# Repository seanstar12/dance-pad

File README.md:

# dance-pad
Code and schematics for Dance Dance Revolution - DDR - FSR sensor upgrade.

# Plan
Use one MEGA238P per arrow to read & convert the 4 FSR values into a pressed/not-pressed signal. 
Use 25 SK6812 LEDs to light up the panel when pressed and show animations when idle.

# Parts
- Arduino-pro-mini clone
- MCP2125 - CAN - interface with Teensy
- Teensy 3.2 - interface with DDR cabinet
- SK6812 - 'Neopixel' LEDs
- FSR - x32 - 4 per tile
- ['Dance Sensor'](https://www.aliexpress.com/item/4000438156295.html) from aliexpress for the TPU shell.
- [FSR](https://www.aliexpress.com/item/4000765691363.html) from aliexpress.

# Why
I have a DDR cabinet, and I am tired of dealing with stuck sensors. This will let me 
calibrate the dance pad on the fly and never have to deal with it again. I've 
wanted to create a CANBus network for a while, and this gives me an excuse to use 
the box of pro-mini clones that I've had for a while now.

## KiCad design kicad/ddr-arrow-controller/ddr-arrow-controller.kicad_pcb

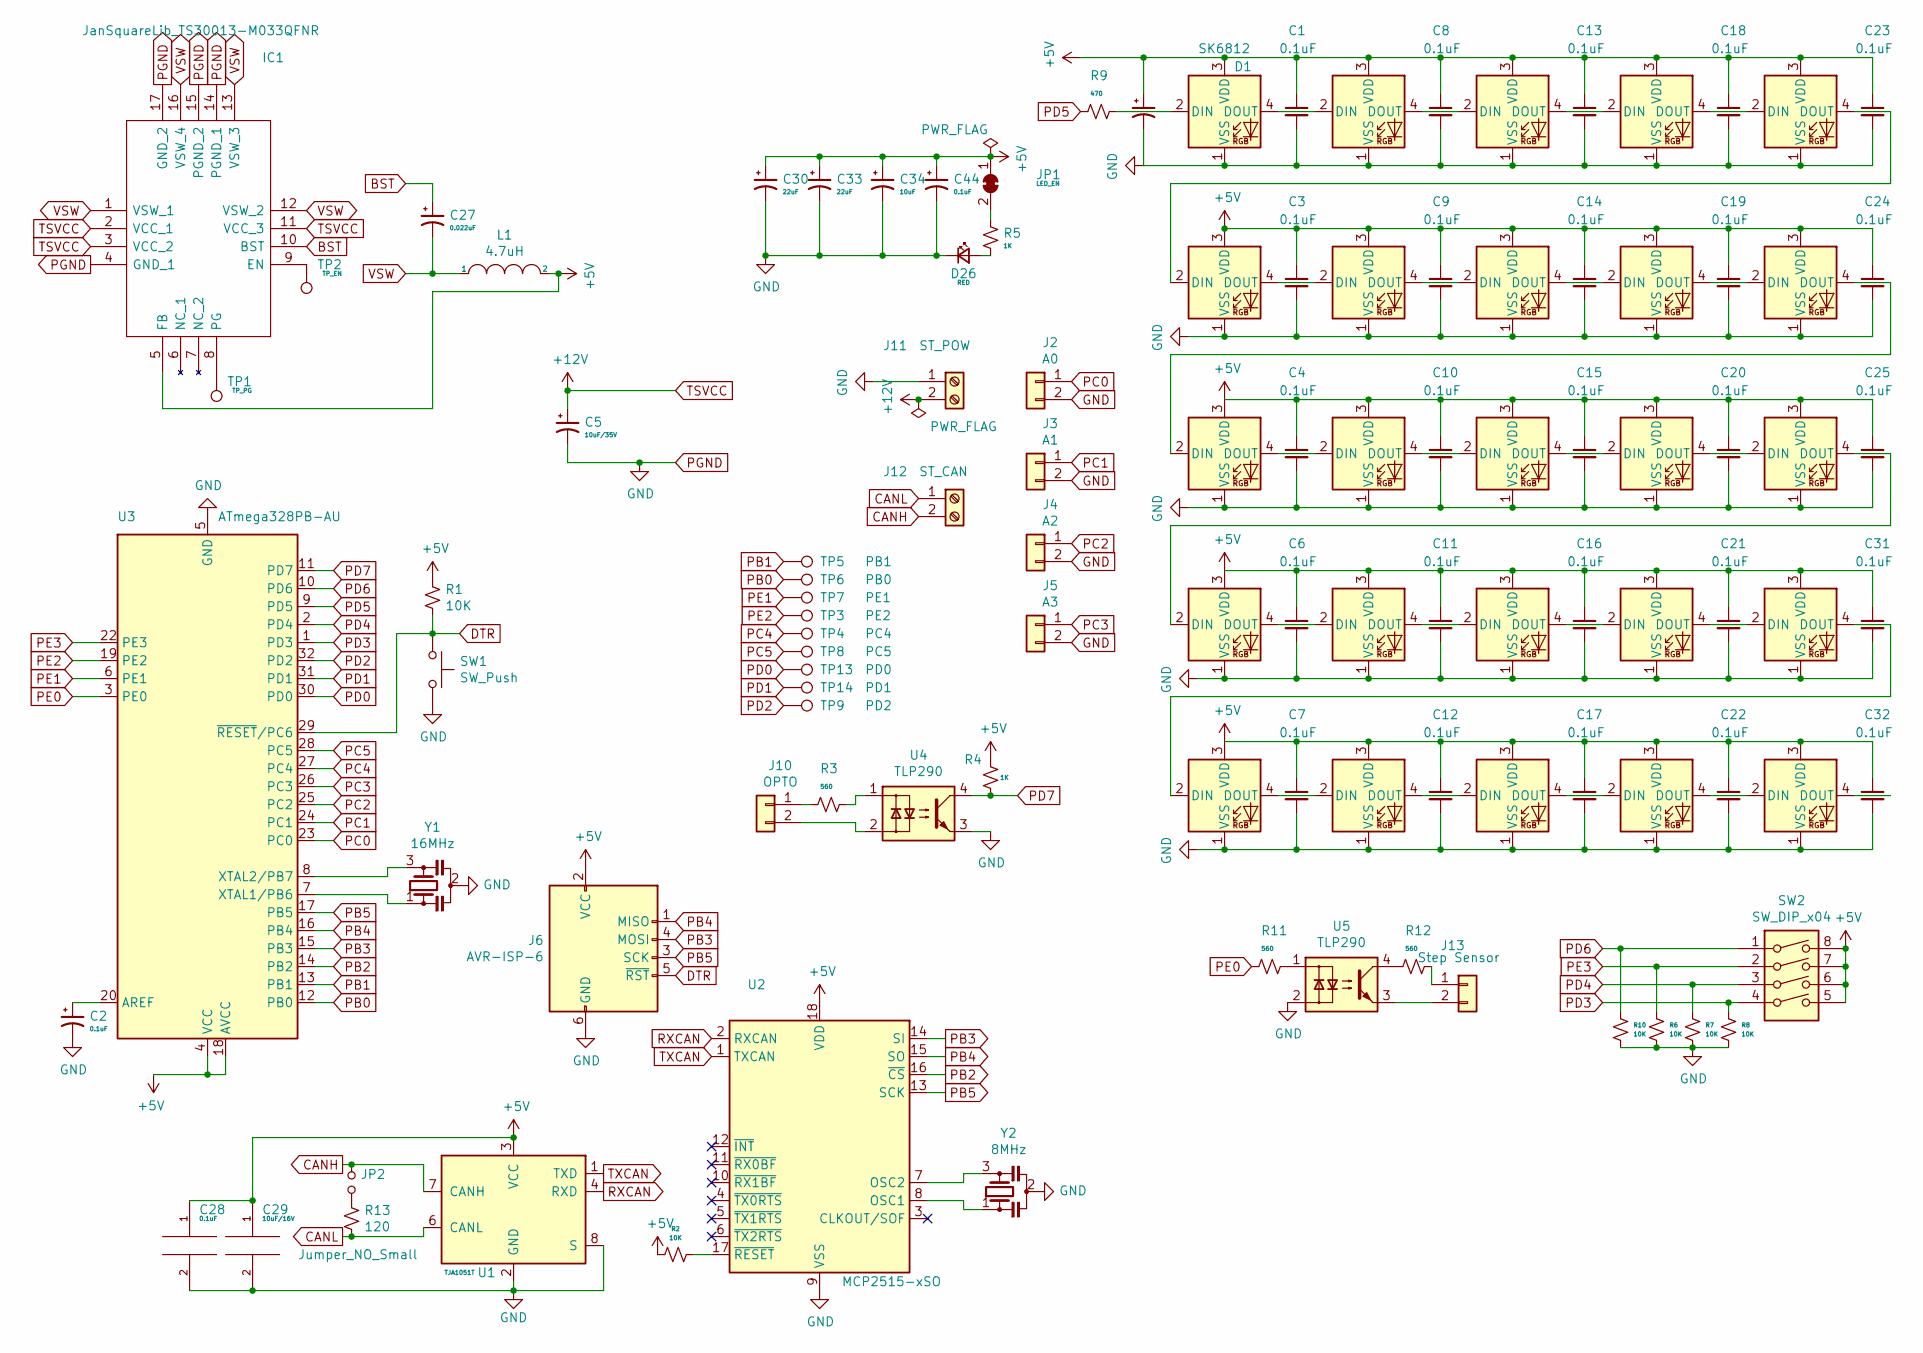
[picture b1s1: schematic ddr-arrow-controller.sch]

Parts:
C1, C2, C3, C4, C6, C7, C8, C9, C10, C11, C12, C13, C14, C15, C16, C17, C18, C19, C20, C21, C22, C23, C24, C25, C28, C31, C32, C44: 0.1uF; C_0805_2012Metric_Pad1.15x1.40mm_HandSolder
C5: 10uF/35V; C_1206_3216Metric_Pad1.42x1.75mm_HandSolder
C27: 0.022uF; C_0805_2012Metric_Pad1.15x1.40mm_HandSolder
C29: 10uF/16V; C_1206_3216Metric_Pad1.42x1.75mm_HandSolder
C30, C33: 22uF; C_0805_2012Metric_Pad1.15x1.40mm_HandSolder
C34: 10uF; C_1206_3216Metric_Pad1.42x1.75mm_HandSolder
C35: 1000uF; C_Elec_10x10.2
D1, D2, D3, D4, D5, D6, D7, D8, D9, D10, D11, D12, D13, D14, D15, D16, D17, D18, D19, D20, D21, D22, D23, D24, D25: SK6812; LED_SK6812_PLCC4_5.0x5.0mm_P3.2mm
D26: RED; LED_0805_2012Metric
IC1: JanSquareLib_TS30013-M033QFNR; QFN50P300X300X100-17N
J2: A0; JST_PH_B2B-PH-K_1x02_P2.00mm_Vertical
J3: A1; JST_PH_B2B-PH-K_1x02_P2.00mm_Vertical
J4: A2; JST_PH_B2B-PH-K_1x02_P2.00mm_Vertical
J5: A3; JST_PH_B2B-PH-K_1x02_P2.00mm_Vertical
J6: AVR-ISP-6; PinHeader_2x03_P2.54mm_Vertical
J10: OPTO; JST_PH_B2B-PH-K_1x02_P2.00mm_Vertical
J11: ST_POW; Molex_Mini-Fit_Jr_5569-02A2_2x01_P4.20mm_Horizontal
J12: ST_CAN; TerminalBlock_Phoenix_MKDS-1,5-2_1x02_P5.00mm_Horizontal
J13: Step Sensor; JST_PH_B2B-PH-K_1x02_P2.00mm_Vertical
JP1: LED_EN; SolderJumper-2_P1.3mm_Bridged_Pad1.0x1.5mm
JP2: Jumper_NO_Small; PinSocket_1x02_P2.54mm_Vertical
L1: 4.7uH; L_Taiyo-Yuden_NR-80xx_HandSoldering
R1, R2, R6, R7, R8, R10: 10K; R_0805_2012Metric_Pad1.15x1.40mm_HandSolder
R3, R11, R12: 560; R_0805_2012Metric_Pad1.15x1.40mm_HandSolder
R4, R5: 1K; R_0805_2012Metric_Pad1.15x1.40mm_HandSolder
R9: 470; R_0805_2012Metric_Pad1.15x1.40mm_HandSolder
R13: 120; R_0805_2012Metric_Pad1.15x1.40mm_HandSolder
SW1: SW_Push; SW_SPST_CK_RS282G05A3
SW2: SW_DIP_x04; SW_DIP_SPSTx04_Slide_9.78x12.34mm_W8.61mm_P2.54mm
TP1: TP_PG; TestPoint_Pad_1.0x1.0mm
TP2: TP_EN; TestPoint_Pad_1.0x1.0mm
TP3: PE2; TestPoint_Pad_1.0x1.0mm
TP4: PC4; TestPoint_Pad_1.0x1.0mm
TP5: PB1; TestPoint_Pad_D2.0mm
TP6: PB0; TestPoint_Pad_D2.0mm
TP7: PE1; TestPoint_Pad_1.0x1.0mm
TP8: PC5; TestPoint_Pad_1.0x1.0mm
TP9: PD2; TestPoint_Pad_D1.0mm
TP13: PD0; TestPoint_Pad_D1.0mm
TP14: PD1; TestPoint_Pad_D1.0mm
U1: TJA1051T; SOIC-8_3.9x4.9mm_P1.27mm
U2: MCP2515-xSO; SOIC-18W_7.5x11.6mm_P1.27mm
U3: ATmega328PB-AU; TQFP-32_7x7mm_P0.8mm
U4, U5: TLP290; SOP-4_4.4x2.6mm_P1.27mm
Y1: 16MHz; Resonator_SMD_muRata_CSTxExxV-3Pin_3.0x1.1mm_HandSoldering
Y2: 8MHz; Resonator_SMD_muRata_CSTxExxV-3Pin_3.0x1.1mm_HandSoldering

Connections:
+5V: C1.1, C3.1, C4.1, C6.1, C7.1, C8.1, C9.1, C10.1, C11.1, C12.1, C13.1, C14.1, C15.1, C16.1, C17.1, C18.1, C19.1, C20.1, C21.1, C22.1, C23.1, C24.1, C25.1, C28.1, C29.1, C30.1, C31.1, C32.1, C33.1, C34.1, C35.1, C44.1, D1.3 (VDD), D2.3 (VDD), D3.3 (VDD), D4.3 (VDD), D5.3 (VDD), D6.3 (VDD), D7.3 (VDD), D8.3 (VDD), D9.3 (VDD), D10.3 (VDD), D11.3 (VDD), D12.3 (VDD), D13.3 (VDD), D14.3 (VDD), D15.3 (VDD), D16.3 (VDD), D17.3 (VDD), D18.3 (VDD), D19.3 (VDD), D20.3 (VDD), D21.3 (VDD), D22.3 (VDD), D23.3 (VDD), D24.3 (VDD), D25.3 (VDD), IC1.5 (FB), J6.2 (VCC), JP1.1 (A), L1.2, R1.1, R2.2, R4.1, SW2.5, SW2.6, SW2.7, SW2.8, U1.3 (VCC), U2.18 (VDD), U3.4 (VCC), U3.18 (AVCC)
BST: C27.1, IC1.10 (BST)
CANH: J12.2, JP2.1, U1.7 (CANH)
CANL: J12.1, R13.2, U1.6 (CANL)
DTR: J6.5 (~RST), R1.2, SW1.1, U3.29 (~RESET~/PC6)
GND: C1.2, C2.2, C3.2, C4.2, C5.2, C6.2, C7.2, C8.2, C9.2, C10.2, C11.2, C12.2, C13.2, C14.2, C15.2, C16.2, C17.2, C18.2, C19.2, C20.2, C21.2, C22.2, C23.2, C24.2, C25.2, C28.2, C29.2, C30.2, C31.2, C32.2, C33.2, C34.2, C35.2, C44.2, D1.1 (VSS), D2.1 (VSS), D3.1 (VSS), D4.1 (VSS), D5.1 (VSS), D6.1 (VSS), D7.1 (VSS), D8.1 (VSS), D9.1 (VSS), D10.1 (VSS), D11.1 (VSS), D12.1 (VSS), D13.1 (VSS), D14.1 (VSS), D15.1 (VSS), D16.1 (VSS), D17.1 (VSS), D18.1 (VSS), D19.1 (VSS), D20.1 (VSS), D21.1 (VSS), D22.1 (VSS), D23.1 (VSS), D24.1 (VSS), D25.1 (VSS), D26.1 (K), IC1.4 (GND_1), IC1.14 (PGND_1), IC1.15 (PGND_2), IC1.17 (GND_2), J2.2, J3.2, J4.2, J5.2, J6.6 (GND), J11.1, R6.2, R7.2, R8.2, R10.2, SW1.2, U1.2 (GND), U1.8 (S), U2.9 (VSS), U3.5 (GND), U3.21 (GND), U4.3, U5.2, Y1.2, Y2.2
unnamed: C2.1, U3.20 (AREF)
unnamed: D1.2 (DIN), R9.1
unnamed: D1.4 (DOUT), D2.2 (DIN)
unnamed: D2.4 (DOUT), D3.2 (DIN)
unnamed: D3.4 (DOUT), D4.2 (DIN)
unnamed: D4.4 (DOUT), D5.2 (DIN)
unnamed: D5.4 (DOUT), D6.2 (DIN)
unnamed: D6.4 (DOUT), D7.2 (DIN)
unnamed: D7.4 (DOUT), D8.2 (DIN)
unnamed: D8.4 (DOUT), D9.2 (DIN)
unnamed: D9.4 (DOUT), D10.2 (DIN)
unnamed: D10.4 (DOUT), D11.2 (DIN)
unnamed: D11.4 (DOUT), D12.2 (DIN)
unnamed: D12.4 (DOUT), D13.2 (DIN)
unnamed: D13.4 (DOUT), D14.2 (DIN)
unnamed: D14.4 (DOUT), D15.2 (DIN)
unnamed: D15.4 (DOUT), D16.2 (DIN)
unnamed: D16.4 (DOUT), D17.2 (DIN)
unnamed: D17.4 (DOUT), D18.2 (DIN)
unnamed: D18.4 (DOUT), D19.2 (DIN)
unnamed: D19.4 (DOUT), D20.2 (DIN)
unnamed: D20.4 (DOUT), D21.2 (DIN)
unnamed: D21.4 (DOUT), D22.2 (DIN)
unnamed: D22.4 (DOUT), D23.2 (DIN)
unnamed: D23.4 (DOUT), D24.2 (DIN)
unnamed: D24.4 (DOUT), D25.2 (DIN)
unnamed: D26.2 (A), R5.2
unnamed: IC1.8 (PG), TP1.1
unnamed: IC1.9 (EN), TP2.1
unnamed: J10.1, R3.2
unnamed: J10.2, U4.2
unnamed: J13.1, R12.1
unnamed: J13.2, U5.3
unnamed: JP1.2 (B), R5.1
unnamed: JP2.2, R13.1
unnamed: R2.1, U2.17 (~RESET)
unnamed: R3.1, U4.1
unnamed: R11.1, U5.1
unnamed: R12.2, U5.4
unnamed: U2.7 (OSC2), Y2.3
unnamed: U2.8 (OSC1), Y2.1
unnamed: U3.7 (XTAL1/PB6), Y1.1
unnamed: U3.8 (XTAL2/PB7), Y1.3
PB0: TP6.1, U3.12 (PB0)
PB1: TP5.1, U3.13 (PB1)
PB2: U2.16 (~CS), U3.14 (PB2)
PB3: J6.4 (MOSI), U2.14 (SI), U3.15 (PB3)
PB4: J6.1 (MISO), U2.15 (SO), U3.16 (PB4)
PB5: J6.3 (SCK), U2.13 (SCK), U3.17 (PB5)
PC0: J2.1, U3.23 (PC0)
PC1: J3.1, U3.24 (PC1)
PC2: J4.1, U3.25 (PC2)
PC3: J5.1, U3.26 (PC3)
PC4: TP4.1, U3.27 (PC4)
PC5: TP8.1, U3.28 (PC5)
PD0: TP13.1, U3.30 (PD0)
PD1: TP14.1, U3.31 (PD1)
PD2: TP9.1, U3.32 (PD2)
PD3: R8.1, SW2.4, U3.1 (PD3)
PD4: R7.1, SW2.3, U3.2 (PD4)
PD5: R9.2, U3.9 (PD5)
PD6: R10.1, SW2.1, U3.10 (PD6)
PD7: R4.2, U3.11 (PD7), U4.4
PE0: R11.2, U3.3 (PE0)
PE1: TP7.1, U3.6 (PE1)
PE2: TP3.1, U3.19 (PE2)
PE3: R6.1, SW2.2, U3.22 (PE3)
RXCAN: U1.4 (RXD), U2.2 (RXCAN)
TSVCC: C5.1, IC1.2 (VCC_1), IC1.3 (VCC_2), IC1.11 (VCC_3), J11.2
TXCAN: U1.1 (TXD), U2.1 (TXCAN)
VSW: C27.2, IC1.1 (VSW_1), IC1.12 (VSW_2), IC1.13 (VSW_3), IC1.16 (VSW_4), L1.1

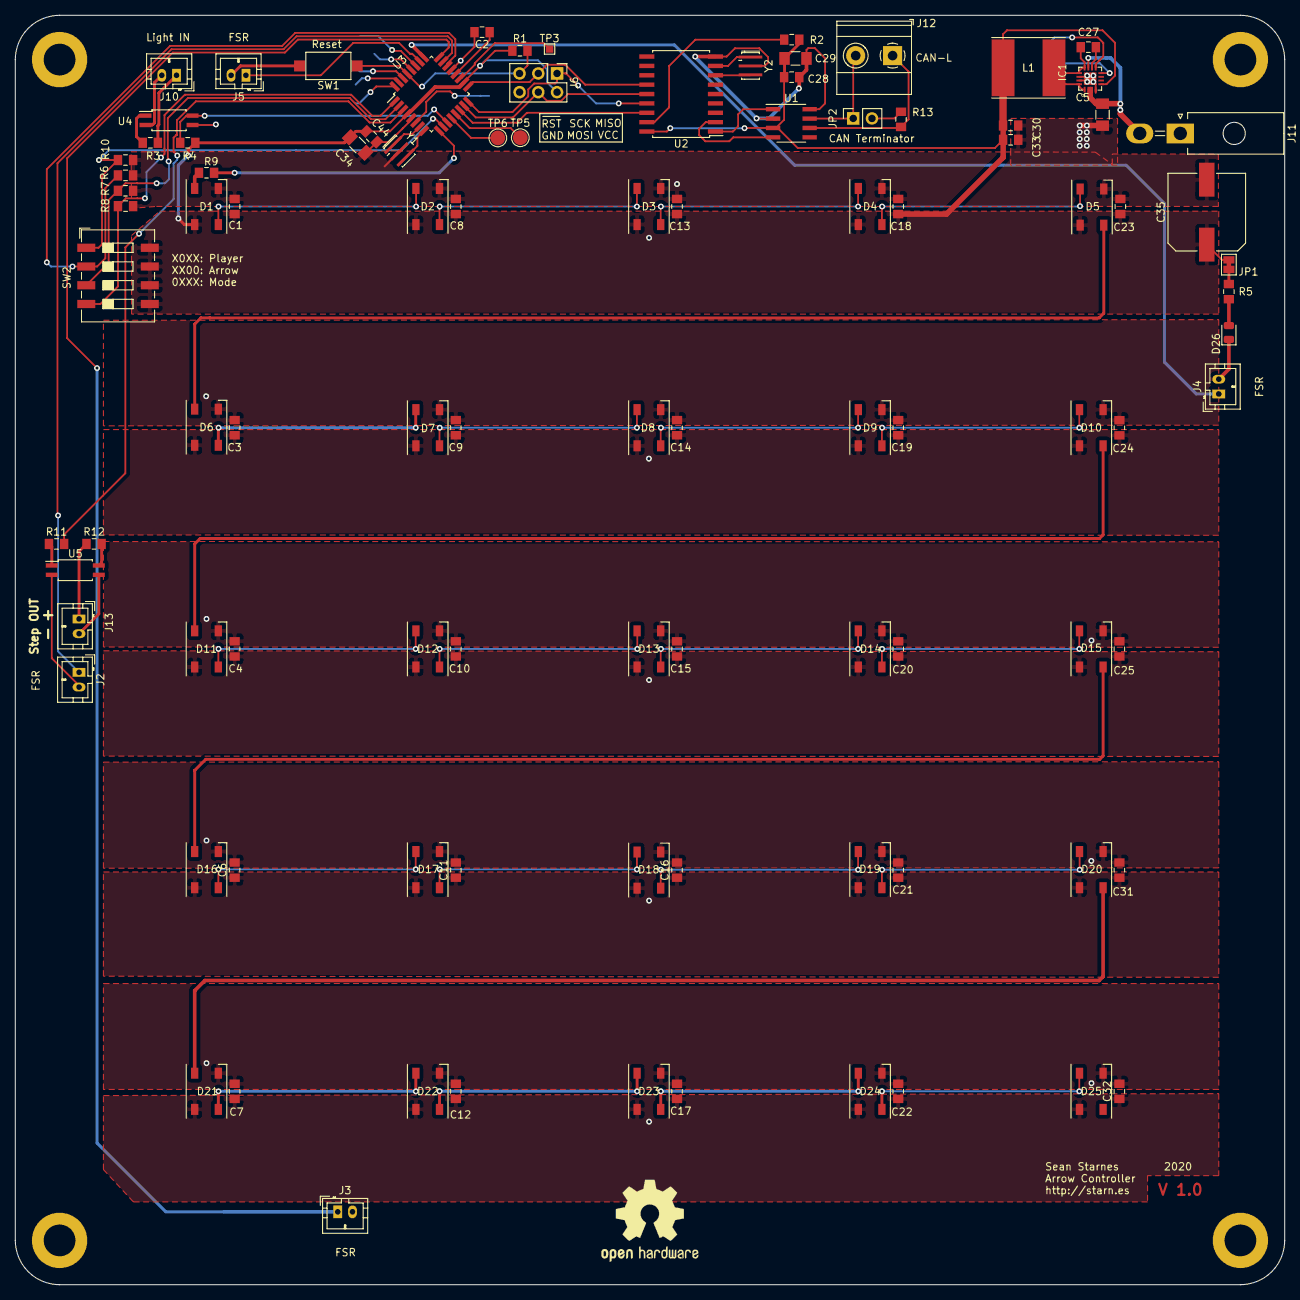
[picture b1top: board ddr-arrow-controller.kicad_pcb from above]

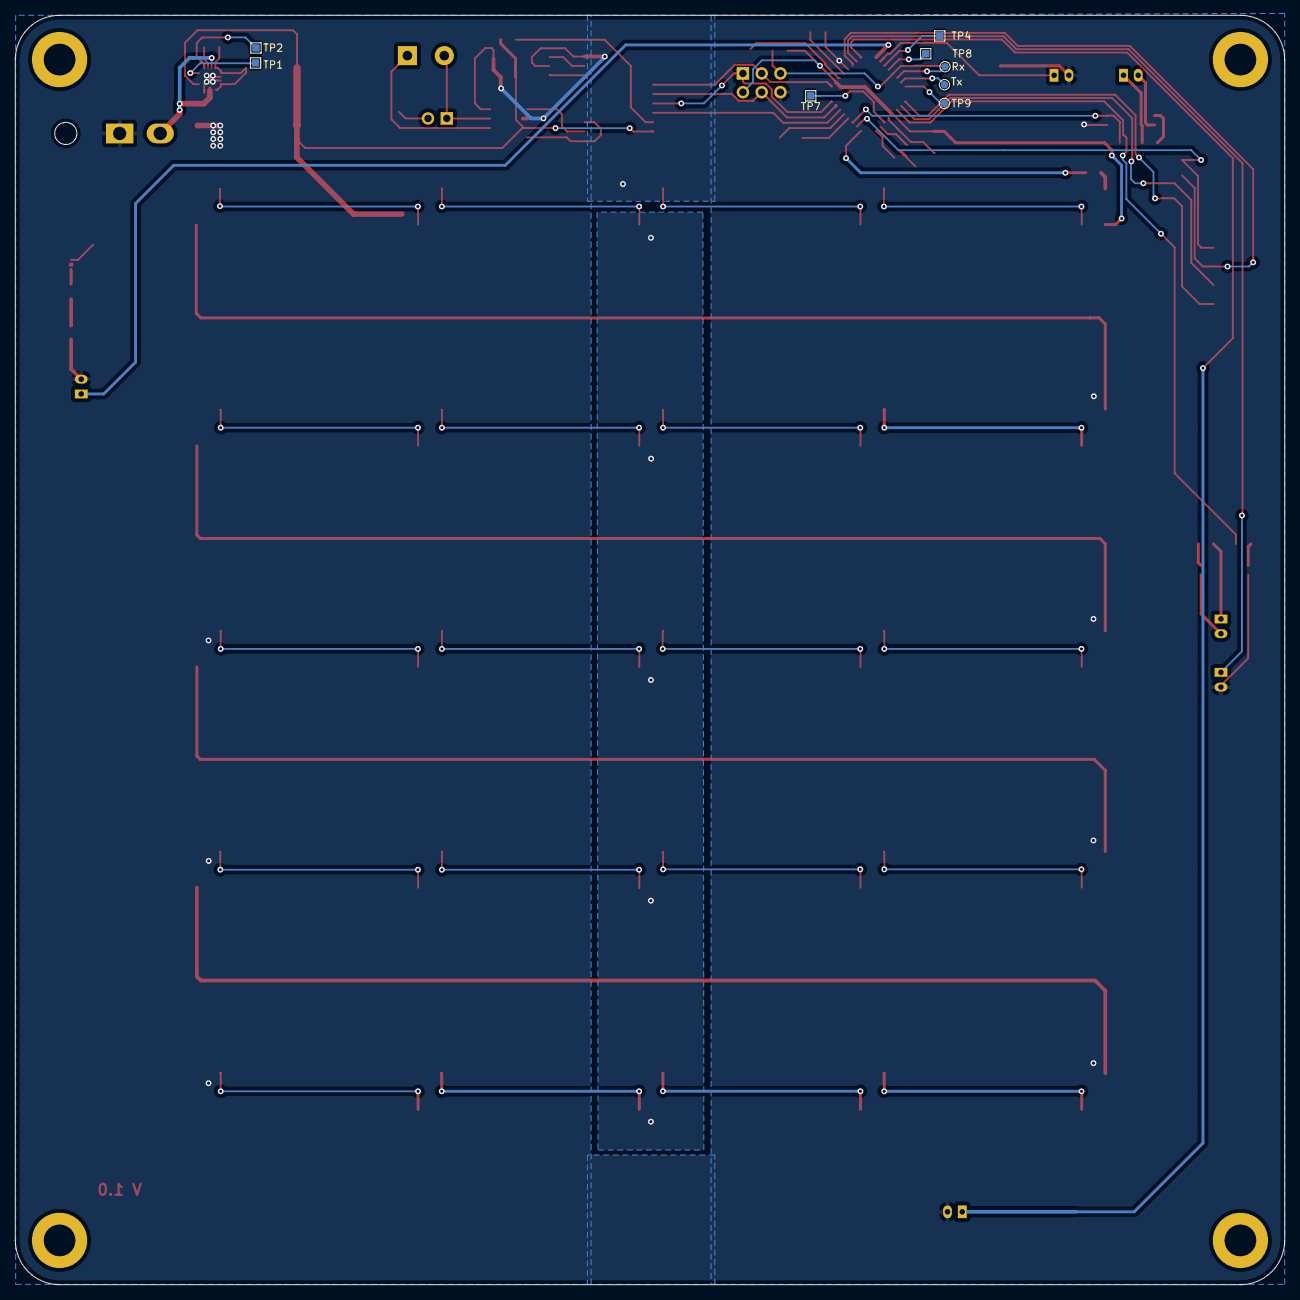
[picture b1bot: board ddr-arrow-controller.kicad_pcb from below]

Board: 2 copper layers, 172.0 x 172.0 mm, 107 parts (8 on the bottom side), 77 nets.

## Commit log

2020-11-05 Initial pad controller code
2020-11-05 Kicad schematic WIP
    added LEDs. started modeling arduino-pro-mini clone footprint.
2020-11-05 Update readme
    Fill in parts, plan, and why.
2020-11-05 Readme Fix
    make parts a list.
2020-11-05 added video to readme.
2020-11-06 Updated Controllers
    Updated pad & teensy controllers for CAN testing.
2020-11-06 Teensy cleanup
2020-11-07 Schematic Updates
    Placed microcontroller, CANBus chips, power regulator.
2020-11-11 Board layout v1 complete
2020-11-13 Rerouted PCB
    Fixed pcb plains. Fixed grounds. Fixed rounded pads. Exported Gerber files.
2020-11-29 Added screenshot of PS
    Add power supply screenshot of TS30013
